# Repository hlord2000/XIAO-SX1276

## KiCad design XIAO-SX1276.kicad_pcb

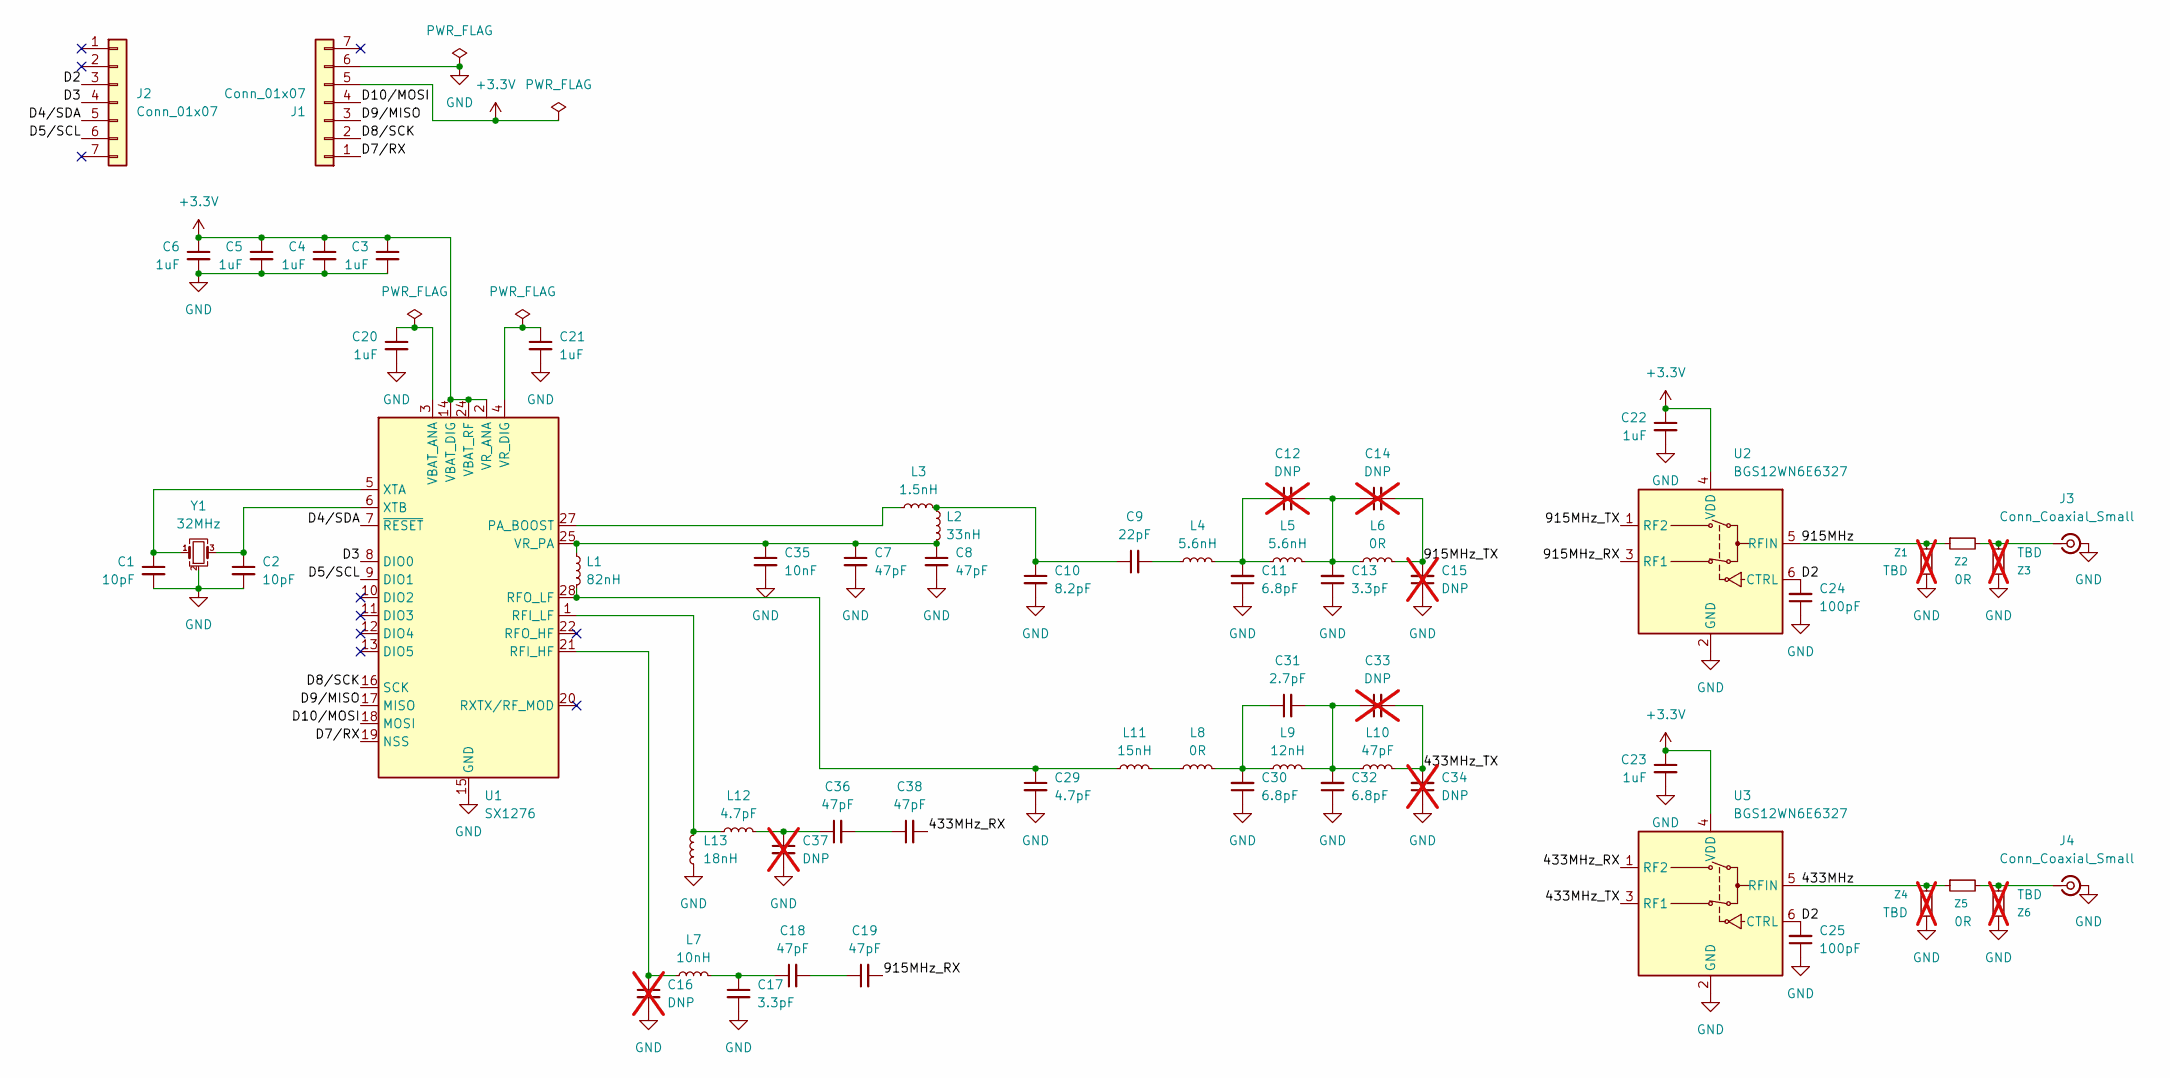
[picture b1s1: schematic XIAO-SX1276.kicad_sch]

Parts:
C1, C2: 10pF; C_0201_0603Metric; LCSC C76921
C3, C4, C5, C6, C20, C21, C22, C23: 1uF; C_0201_0603Metric; LCSC C76935
C7, C8, C18, C19, C36, C38: 47pF; C_0201_0603Metric; LCSC C85908
C9: 22pF; C_0201_0603Metric; LCSC C76924
C10: 8.2pF; C_0201_0603Metric; LCSC C85918
C11, C30, C32: 6.8pF; C_0201_0603Metric; LCSC C338045
C12, C14, C15, C16, C33, C34, C37: DNP; C_0201_0603Metric; not fitted
C13, C17: 3.3pF; C_0201_0603Metric; LCSC C85906
C24, C25: 100pF; C_0201_0603Metric; LCSC C76922
C29: 4.7pF; C_0201_0603Metric; LCSC C161428
C31: 2.7pF; C_0201_0603Metric; LCSC C85902
C35: 10nF; C_0201_0603Metric; LCSC C85930
J1, J2: Conn_01x07; H7-HALF-HOLE-2.54
J3, J4: Conn_Coaxial_Small; U.FL_Hirose_U.FL-R-SMT-1_Vertical; LCSC C88374
L1: 82nH; L_0201_0603Metric; LCSC C1857896
L2: 33nH; L_0201_0603Metric; LCSC C162611
L3: 1.5nH; L_0201_0603Metric; LCSC C77114
L4, L5: 5.6nH; L_0201_0603Metric; LCSC C237444
L6, L8: 0R; L_0201_0603Metric; LCSC C22458608
L7: 10nH; L_0201_0603Metric; LCSC C162594
L9: 12nH; L_0201_0603Metric; LCSC C162597
L10: 47pF; L_0201_0603Metric; LCSC C85908
L11: 15nH; L_0201_0603Metric; LCSC C98038
L12: 4.7pF; L_0201_0603Metric; LCSC C161428
L13: 18nH; L_0201_0603Metric; LCSC C162600
U1: SX1276; QFN-28-1EP_6x6mm_P0.65mm_EP4.8x4.8mm_ThermalVias; LCSC C80171
U2, U3: BGS12WN6E6327; Infineon_PG-TSNP-6-10_0.7x1.1mm_0.7x1.1mm_P0.4mm; LCSC C1854968
Y1: 32MHz; Crystal_SMD_1210-4Pin_1.2x1.0mm; LCSC C19858538
Z1, Z3, Z4, Z6: TBD; C_0201_0603Metric; not fitted
Z2, Z5: 0R; C_0201_0603Metric; LCSC C22458608

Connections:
+3.3V: C3.1, C4.1, C5.1, C6.1, C22.1, C23.1, J1.5, U1.2 (VR_ANA), U1.14 (VBAT_DIG), U1.24 (VBAT_RF), U2.4 (VDD), U3.4 (VDD)
/433MHz: U3.5 (RFIN), Z4.1, Z5.1
/433MHz_RX: C38.2, U3.1 (RF2)
/433MHz_TX: C33.2, C34.2, L10.2, U3.3 (RF1)
/915MHz: U2.5 (RFIN), Z1.1, Z2.1
/915MHz_RX: C19.2, U2.3 (RF1)
/915MHz_TX: C14.2, C15.2, L6.2, U2.1 (RF2)
/D2: C24.2, C25.2, J2.3, U2.6 (CTRL), U3.6 (CTRL)
/D3: J2.4, U1.8 (DIO0)
/D4/SDA: J2.5, U1.7 (~RESET)
/D5/SCL: J2.6, U1.9 (DIO1)
/D7/RX: J1.1, U1.19 (NSS)
/D8/SCK: J1.2, U1.16 (SCK)
/D9/MISO: J1.3, U1.17 (MISO)
/D10/MOSI: J1.4, U1.18 (MOSI)
GND: C1.2, C2.2, C3.2, C4.2, C5.2, C6.2, C7.2, C8.2, C10.2, C11.1, C13.1, C15.1, C16.2, C17.2, C20.2, C21.2, C22.2, C23.2, C24.1, C25.1, C29.2, C30.1, C32.1, C34.1, C35.2, C37.2, J1.6, J3.2 (Ext), J4.2 (Ext), L13.1, U1.15 (GND), U1.23 (GND), U1.26 (GND), U1.29 (GND), U2.2 (GND), U3.2 (GND), Y1.2 (G), Y1.4 (G), Z1.2, Z3.1, Z4.2, Z6.1
unnamed: C9.2, L4.1
unnamed: C9.1, C10.1, L2.1, L3.2
unnamed: C11.2, C12.1, L4.2, L5.1
unnamed: C12.2, C13.2, C14.1, L5.2, L6.1
unnamed: C17.1, C18.1, L7.2
unnamed: C18.2, C19.1
unnamed: C30.2, C31.1, L8.2, L9.1
unnamed: C31.2, C32.2, C33.1, L9.2, L10.1
unnamed: C36.1, C37.1, L12.2
unnamed: C36.2, C38.1
unnamed: J3.1 (In), Z2.2, Z3.2
unnamed: J4.1 (In), Z5.2, Z6.2
unnamed: L8.1, L11.2
unnamed: L3.1, U1.27 (PA_BOOST)
unnamed: C16.1, L7.1, U1.21 (RFI_HF)
unnamed: L12.1, L13.2, U1.1 (RFI_LF)
unnamed: C29.1, L1.2, L11.1, U1.28 (RFO_LF)
unnamed: C20.1, U1.3 (VBAT_ANA)
unnamed: C21.1, U1.4 (VR_DIG)
unnamed: C7.1, C8.1, C35.1, L1.1, L2.2, U1.25 (VR_PA)
unnamed: C1.1, U1.5 (XTA), Y1.1
unnamed: C2.1, U1.6 (XTB), Y1.3

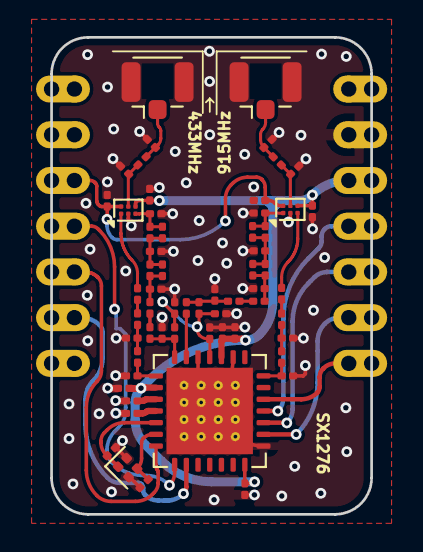
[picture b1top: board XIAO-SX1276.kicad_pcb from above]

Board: 4 copper layers, 17.8 x 26.5 mm, 62 parts (0 on the bottom side), 38 nets.

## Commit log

2026-02-25 Initial commit.
2026-03-10 Updated BOM
